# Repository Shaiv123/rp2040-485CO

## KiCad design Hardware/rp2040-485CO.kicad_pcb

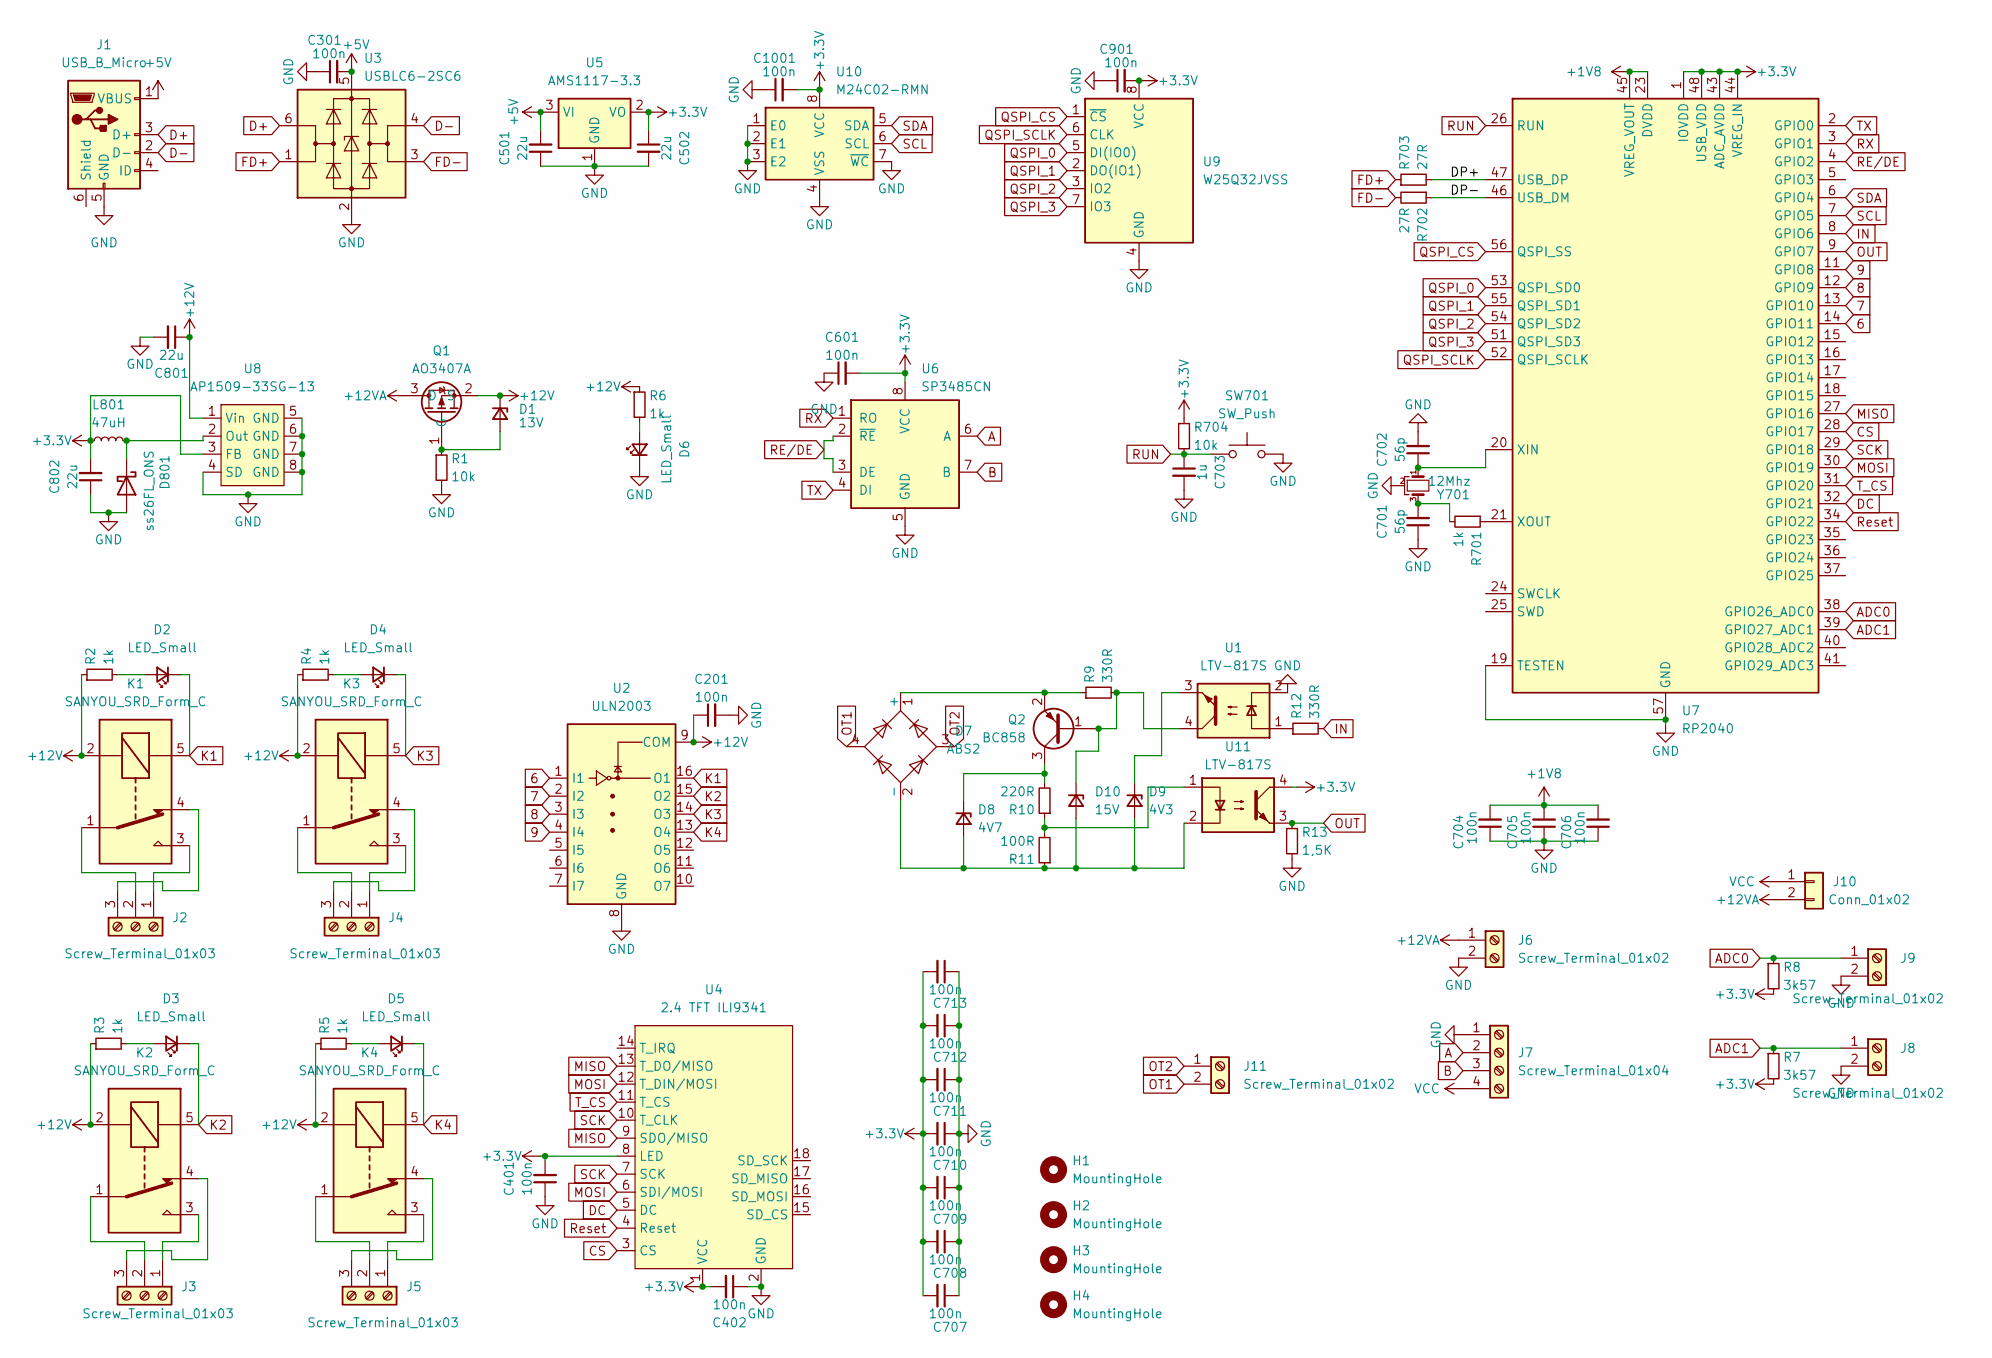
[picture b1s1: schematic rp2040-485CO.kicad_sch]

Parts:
C201, C301, C401, C402, C601, C901, C1001: 100n; C_0805_2012Metric_Pad1.18x1.45mm_HandSolder
C501, C502, C801, C802: 22u; C_0805_2012Metric_Pad1.18x1.45mm_HandSolder
C701, C702: 56p; C_0603_1608Metric_Pad1.08x0.95mm_HandSolder
C703: 1u; C_0805_2012Metric_Pad1.18x1.45mm_HandSolder
C704, C705, C706, C707, C708, C709, C710, C711, C712, C713: 100n; C_0603_1608Metric_Pad1.08x0.95mm_HandSolder
D1: 13V; D_SOD-323_HandSoldering
D2, D3, D4, D5, D6: LED_Small; LED_0805_2012Metric_Pad1.15x1.40mm_HandSolder
D7: ABS2; Diode_Bridge_Diotec_ABS
D8: 4V7; D_0805_2012Metric_Pad1.15x1.40mm_HandSolder
D9: 4V3; D_0805_2012Metric_Pad1.15x1.40mm_HandSolder
D10: 15V; D_0805_2012Metric_Pad1.15x1.40mm_HandSolder
D801: ss26FL_ONS; D_SOD-123F
H1, H2, H3, H4: MountingHole; MountingHole_3.2mm_M3_Pad
J1: USB_B_Micro; USB_Micro-B_Amphenol_10118194_Horizontal
J2, J3, J4, J5: Screw_Terminal_01x03; TerminalBlock_Phoenix_MKDS-1,5-3_1x03_P5.00mm_Horizontal
J6, J8, J9, J11: Screw_Terminal_01x02; PhoenixContact_MC_1,5_2-G-3.5_1x02_P3.50mm_Horizontal
J7: Screw_Terminal_01x04; PhoenixContact_MC_1,5_4-G-3.81_1x04_P3.81mm_Horizontal
J10: Conn_01x02; PinHeader_1x02_P2.54mm_Vertical
K1, K2, K3, K4: SANYOU_SRD_Form_C; Relay_SPDT_SANYOU_SRD_Series_Form_C
L801: 47uH; L_12x12mm_H6mm
Q1: AO3407A; SOT-23-3
Q2: BC858; SOT-23
R1, R704: 10k; R_0805_2012Metric_Pad1.20x1.40mm_HandSolder
R2, R3, R4, R5, R6, R701: 1k; R_0805_2012Metric_Pad1.20x1.40mm_HandSolder
R7, R8: 3k57; R_0805_2012Metric_Pad1.20x1.40mm_HandSolder
R9, R12: 330R; R_0805_2012Metric_Pad1.20x1.40mm_HandSolder
R10: 220R; R_0805_2012Metric_Pad1.20x1.40mm_HandSolder
R11: 100R; R_0805_2012Metric_Pad1.20x1.40mm_HandSolder
R13: 1,5K; R_0805_2012Metric_Pad1.20x1.40mm_HandSolder
R702, R703: 27R; R_0805_2012Metric_Pad1.20x1.40mm_HandSolder
SW701: SW_Push; SW_Push_SPST_NO_Alps_SKRK
U1, U11: LTV-817S; SMDIP-4_W9.53mm
U2: ULN2003; SO-16_3.9x9.9mm_P1.27mm
U3: USBLC6-2SC6; SOT-23-6
U4: 2.4 TFT ILI9341; 2.4 tft ILI9341
U5: AMS1117-3.3; SOT-223-3_TabPin2
U6: SP3485CN; SOIC-8_3.9x4.9mm_P1.27mm
U7: RP2040; QFN-56-1EP_7x7mm_P0.4mm_EP3.2x3.2mm
U8: AP1509-33SG-13; SOP-8_3.9x4.9mm_P1.27mm
U9: W25Q32JVSS; SOIC-8_5.23x5.23mm_P1.27mm
U10: M24C02-RMN; SOIC-8_3.9x4.9mm_P1.27mm
Y701: 12Mhz; Resonator_SMD_Murata_CSTxExxV-3Pin_3.0x1.1mm_HandSoldering

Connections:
6: U2.1 (I1), U7.14 (GPIO11)
7: U2.2 (I2), U7.13 (GPIO10)
8: U2.3 (I3), U7.12 (GPIO9)
9: U2.4 (I4), U7.11 (GPIO8)
+1V8: C704.2, C705.2, C706.2, U7.23 (DVDD), U7.45 (VREG_VOUT), U7.50 (DVDD)
+3.3V: C401.2, C402.2, C502.1, C601.2, C707.2, C708.2, C709.2, C710.2, C711.2, C712.2, C713.2, C802.2, C901.2, C1001.2, L801.1, R7.2, R8.2, R704.1, U4.1 (VCC), U4.8 (LED), U5.2 (VO), U6.8 (VCC), U7.1 (IOVDD), U7.10 (IOVDD), U7.22 (IOVDD), U7.33 (IOVDD), U7.42 (IOVDD), U7.43 (ADC_AVDD), U7.44 (VREG_IN), U7.48 (USB_VDD), U7.49 (IOVDD), U8.3 (FB), U9.8 (VCC), U10.8 (VCC), U11.4
+5V: C301.2, C501.2, J1.1 (VBUS), U3.5 (VBUS), U5.3 (VI)
+12V: C201.1, C801.1, D1.1 (K), K1.2, K2.2, K3.2, K4.2, Q1.2 (S), R2.1, R3.1, R4.1, R5.1, R6.1, U2.9 (COM), U8.1 (Vin)
+12VA: J6.1, J10.2, Q1.3 (D)
/DP+: R703.2, U7.47 (USB_DP)
/DP-: R702.1, U7.46 (USB_DM)
A: J7.2, U6.6 (A)
ADC0: J9.1, R8.1, U7.38 (GPIO26_ADC0)
ADC1: J8.1, R7.1, U7.39 (GPIO27_ADC1)
B: J7.3, U6.7 (B)
CS: U4.3 (CS), U7.28 (GPIO17)
D+: J1.3 (D+), U3.6 (I/O1)
D-: J1.2 (D-), U3.4 (I/O2)
DC: U4.5 (DC), U7.32 (GPIO21)
FD+: R703.1, U3.1 (I/O1)
FD-: R702.2, U3.3 (I/O2)
GND: C201.2, C301.1, C401.1, C402.1, C501.1, C502.2, C601.1, C701.1, C702.2, C703.2, C704.1, C705.1, C706.1, C707.1, C708.1, C709.1, C710.1, C711.1, C712.1, C713.1, C801.2, C802.1, C901.1, C1001.1, D6.1 (K), D801.2 (A), J1.5 (GND), J6.2, J7.1, J8.2, J9.2, R1.2, R13.2, SW701.2, U1.2, U2.8 (GND), U3.2 (GND), U4.2 (GND), U5.1 (GND), U6.5 (GND), U7.19 (TESTEN), U7.57 (GND), U8.4 (SD), U8.5 (GND), U8.6 (GND), U8.7 (GND), U8.8 (GND), U9.4 (GND), U10.1 (E0), U10.2 (E1), U10.3 (E2), U10.4 (VSS), U10.7 (~WC), Y701.2
IN: R12.2, U7.8 (GPIO6)
K1: D2.1 (K), K1.5, U2.16 (O1)
K2: D3.1 (K), K2.5, U2.15 (O2)
K3: D4.1 (K), K3.5, U2.14 (O3)
K4: D5.1 (K), K4.5, U2.13 (O4)
MISO: U4.9 (SDO/MISO), U4.13 (T_DO/MISO), U7.27 (GPIO16)
MOSI: U4.6 (SDI/MOSI), U4.12 (T_DIN/MOSI), U7.30 (GPIO19)
unnamed: C701.2, R701.2, Y701.3
unnamed: D1.2 (A), Q1.1 (G), R1.1
unnamed: D2.2 (A), R2.2
unnamed: D3.2 (A), R3.2
unnamed: D4.2 (A), R4.2
unnamed: D5.2 (A), R5.2
unnamed: D6.2 (A), R6.2
unnamed: D7.1 (+), Q2.2 (E), R9.1
unnamed: D8.1 (K), Q2.3 (C), R10.2
unnamed: D9.1 (K), U1.3
unnamed: D7.2 (-), D8.2 (A), D9.2 (A), D10.2 (A), R11.1, U11.2
unnamed: D10.1 (K), Q2.1 (B), R9.2, U1.4
unnamed: D801.1 (K), L801.2, U8.2 (Out)
unnamed: J2.1, K1.3
unnamed: J2.2, K1.1
unnamed: J2.3, K1.4
unnamed: J3.1, K2.3
unnamed: J3.2, K2.1
unnamed: J3.3, K2.4
unnamed: J4.1, K3.3
unnamed: J4.2, K3.1
unnamed: J4.3, K3.4
unnamed: J5.1, K4.3
unnamed: J5.2, K4.1
unnamed: J5.3, K4.4
unnamed: R10.1, R11.2, U11.1
unnamed: R12.1, U1.1
unnamed: C702.1, U7.20 (XIN), Y701.1
unnamed: R701.1, U7.21 (XOUT)
OT1: D7.4, J11.2
OT2: D7.3, J11.1
OUT: R13.1, U7.9 (GPIO7), U11.3
QSPI_0: U7.53 (QSPI_SD0), U9.5 (DI(IO0))
QSPI_1: U7.55 (QSPI_SD1), U9.2 (DO(IO1))
QSPI_2: U7.54 (QSPI_SD2), U9.3 (IO2)
QSPI_3: U7.51 (QSPI_SD3), U9.7 (IO3)
QSPI_CS: U7.56 (QSPI_SS), U9.1 (~CS)
QSPI_SCLK: U7.52 (QSPI_SCLK), U9.6 (CLK)
RE/DE: U6.2 (~RE), U6.3 (DE), U7.4 (GPIO2)
RUN: C703.1, R704.2, SW701.1, U7.26 (RUN)
RX: U6.1 (RO), U7.3 (GPIO1)
Reset: U4.4 (Reset), U7.34 (GPIO22)
SCK: U4.7 (SCK), U4.10 (T_CLK), U7.29 (GPIO18)
SCL: U7.7 (GPIO5), U10.6 (SCL)
SDA: U7.6 (GPIO4), U10.5 (SDA)
TX: U6.4 (DI), U7.2 (GPIO0)
T_CS: U4.11 (T_CS), U7.31 (GPIO20)
VCC: J7.4, J10.1

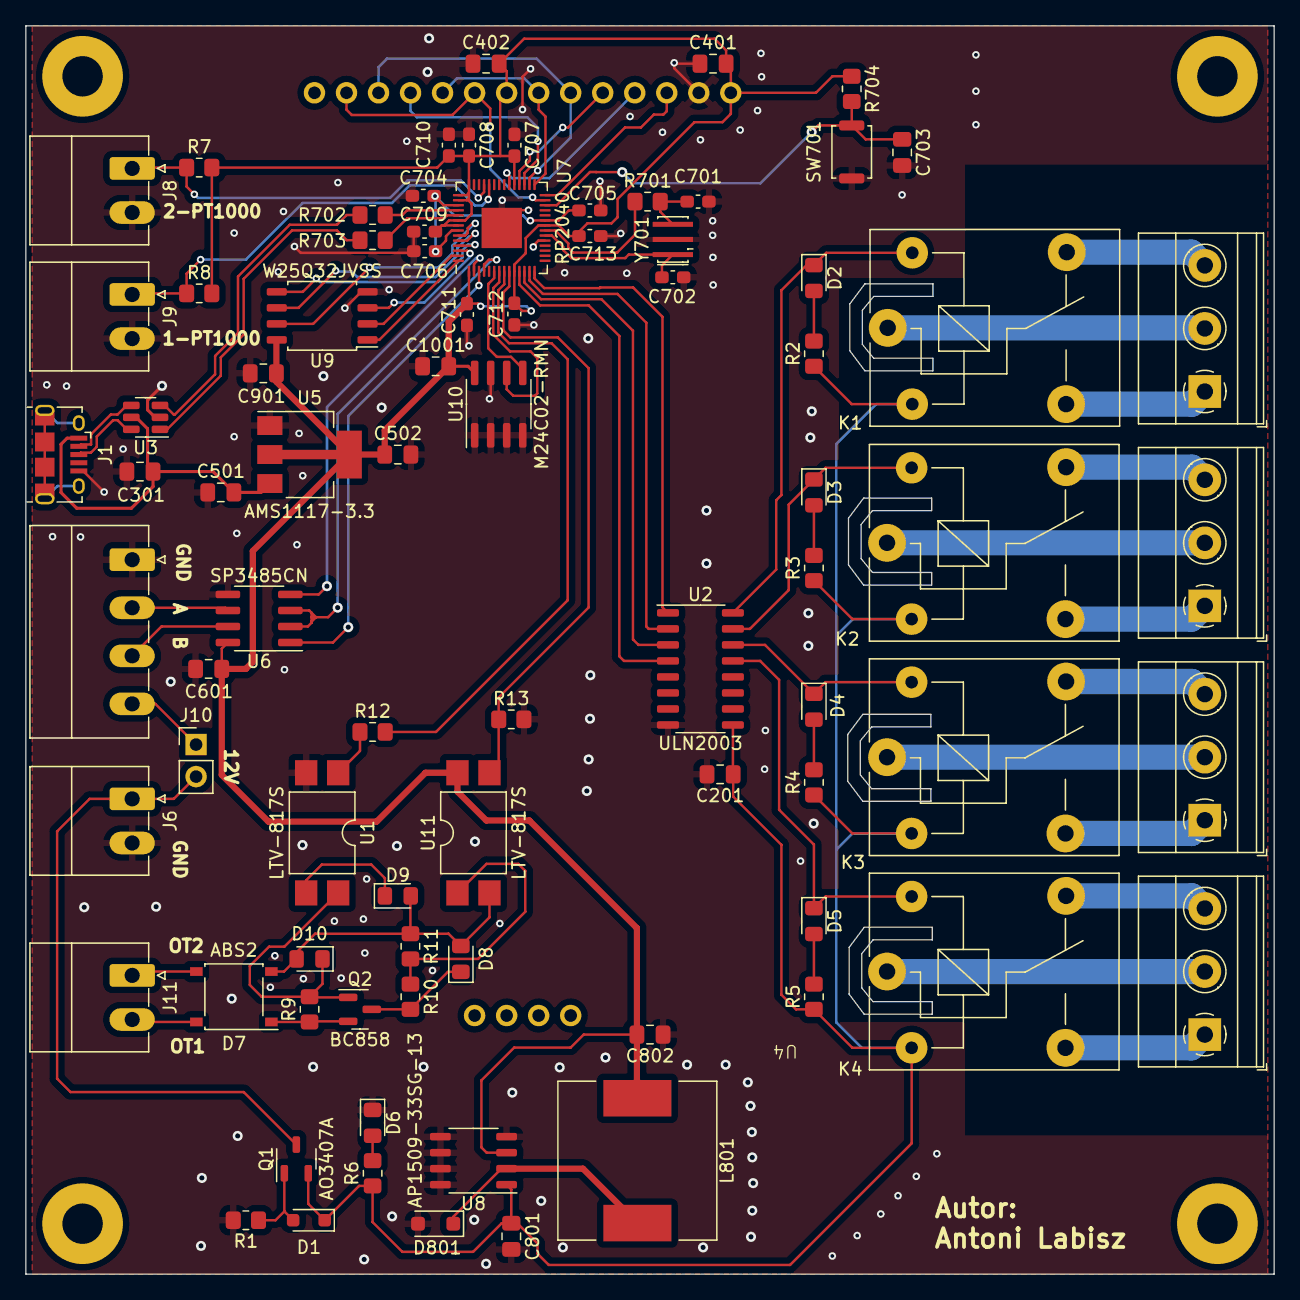
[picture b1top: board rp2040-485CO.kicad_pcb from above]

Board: 2 copper layers, 99.0 x 99.0 mm, 87 parts (0 on the bottom side), 77 nets.

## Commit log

2024-10-13 Init
